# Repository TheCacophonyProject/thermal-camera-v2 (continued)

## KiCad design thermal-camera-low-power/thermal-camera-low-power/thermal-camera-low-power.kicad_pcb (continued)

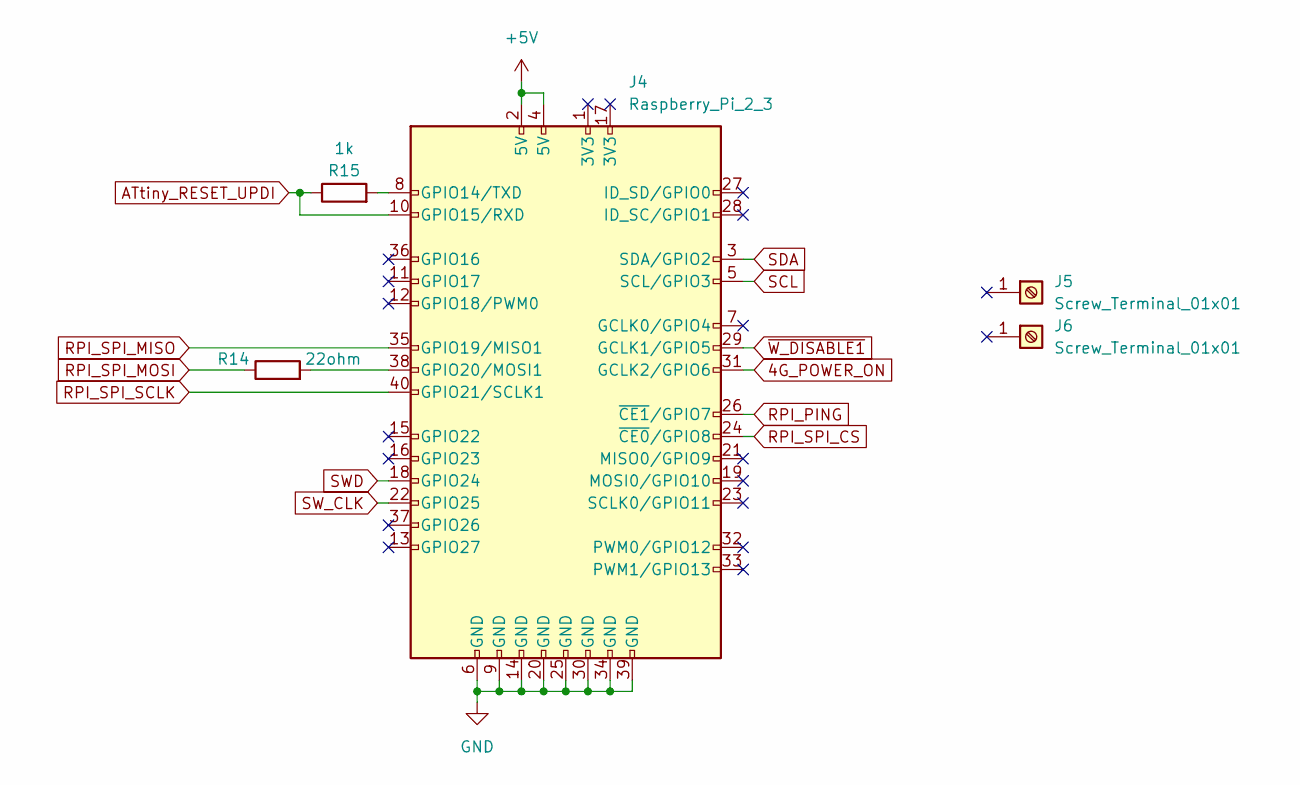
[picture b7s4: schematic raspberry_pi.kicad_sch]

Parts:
J4: Raspberry_Pi_2_3; RPi_2_W_SMD; LCSC C3975165
J5, J6: Screw_Terminal_01x01; SMD_BD4.4-L4.4-D2.8; LCSC C2928178
R14: 22ohm; R_0402_1005Metric; LCSC C25092
R15: 1k; R_0402_1005Metric; LCSC C11702

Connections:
4G_POWER_ON: J4.31 (GCLK2/GPIO6); also elsewhere on the board
+5V: J4.2 (5V), J4.4 (5V); also elsewhere on the board
ATtiny_RESET_UPDI: J4.10 (GPIO15/RXD), R15.1; also elsewhere on the board
GND: J4.6 (GND), J4.9 (GND), J4.14 (GND), J4.20 (GND), J4.25 (GND), J4.30 (GND), J4.34 (GND), J4.39 (GND); also elsewhere on the board
unnamed: J4.8 (GPIO14/TXD), R15.2
unnamed: J4.38 (GPIO20/MOSI1), R14.2
RPI_PING: J4.26 (~CE1/GPIO7); also elsewhere on the board
RPI_SPI_CS: J4.24 (~CE0/GPIO8); also elsewhere on the board
RPI_SPI_MISO: J4.35 (GPIO19/MISO1); also elsewhere on the board
RPI_SPI_MOSI: R14.1; also elsewhere on the board
RPI_SPI_SCLK: J4.40 (GPIO21/SCLK1); also elsewhere on the board
SCL: J4.5 (SCL/GPIO3); also elsewhere on the board
SDA: J4.3 (SDA/GPIO2); also elsewhere on the board
SWD: J4.18 (GPIO24); also elsewhere on the board
SW_CLK: J4.22 (GPIO25); also elsewhere on the board
~W_DISABLE1: J4.29 (GCLK1/GPIO5); also elsewhere on the board

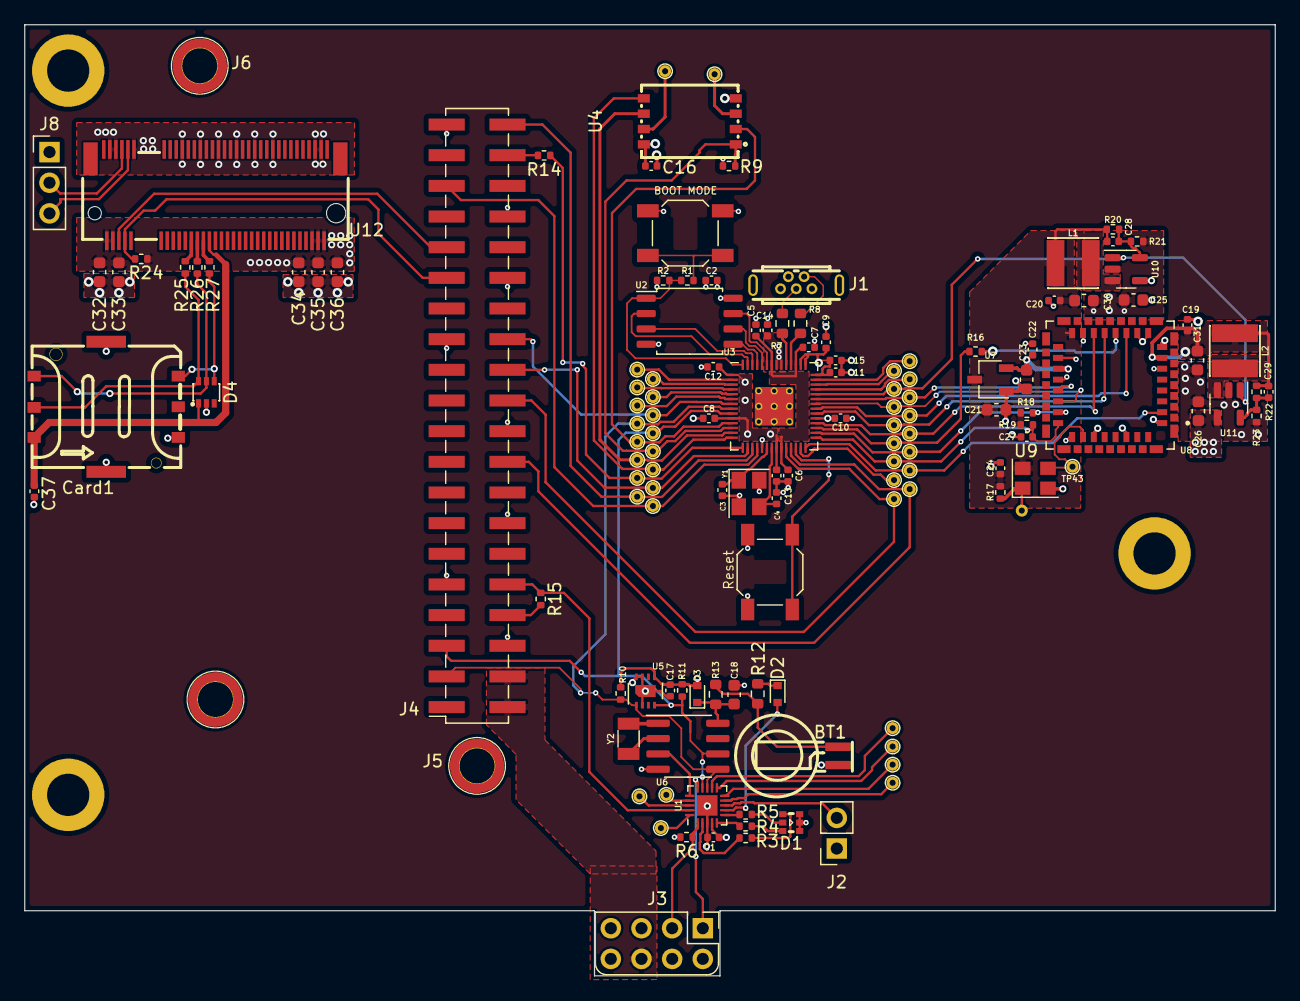
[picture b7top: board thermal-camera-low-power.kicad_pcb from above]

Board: 4 copper layers, 103.6 x 78.8 mm, 142 parts (1 on the bottom side), 99 nets.

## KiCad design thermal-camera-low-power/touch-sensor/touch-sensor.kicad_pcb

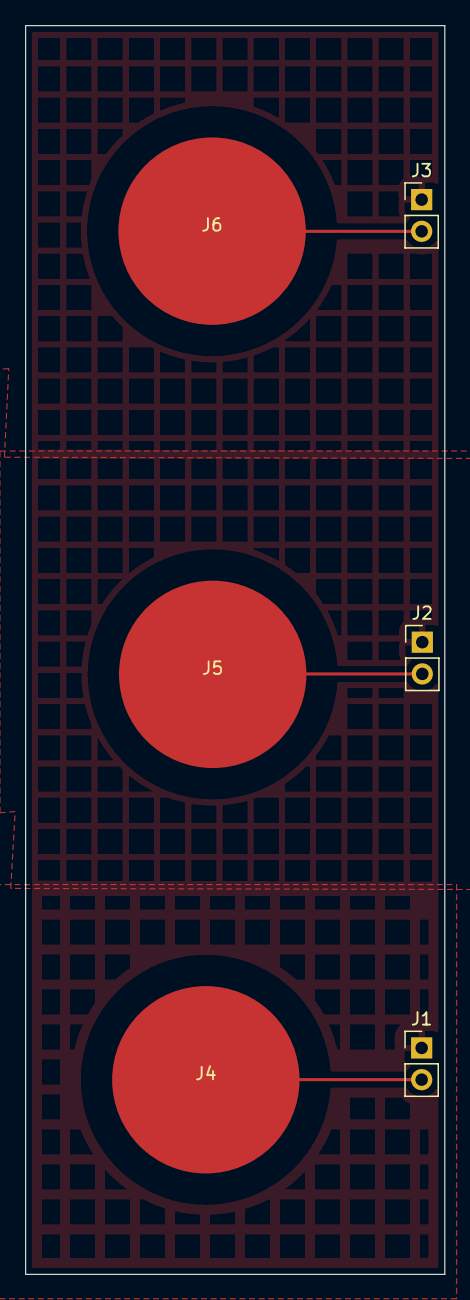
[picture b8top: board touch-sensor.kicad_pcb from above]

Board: 2 copper layers, 33.5 x 100.0 mm, 6 parts (0 on the bottom side), 4 nets.

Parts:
J1, J2, J3: Conn_01x02; PinHeader_1x02_P2.54mm_Vertical
J4, J5, J6: Conn_01x01; touch_15mm

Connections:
GND: J1.1, J2.1, J3.1
unnamed: J1.2, J4.1
unnamed: J2.2, J5.1
unnamed: J3.2, J6.1
